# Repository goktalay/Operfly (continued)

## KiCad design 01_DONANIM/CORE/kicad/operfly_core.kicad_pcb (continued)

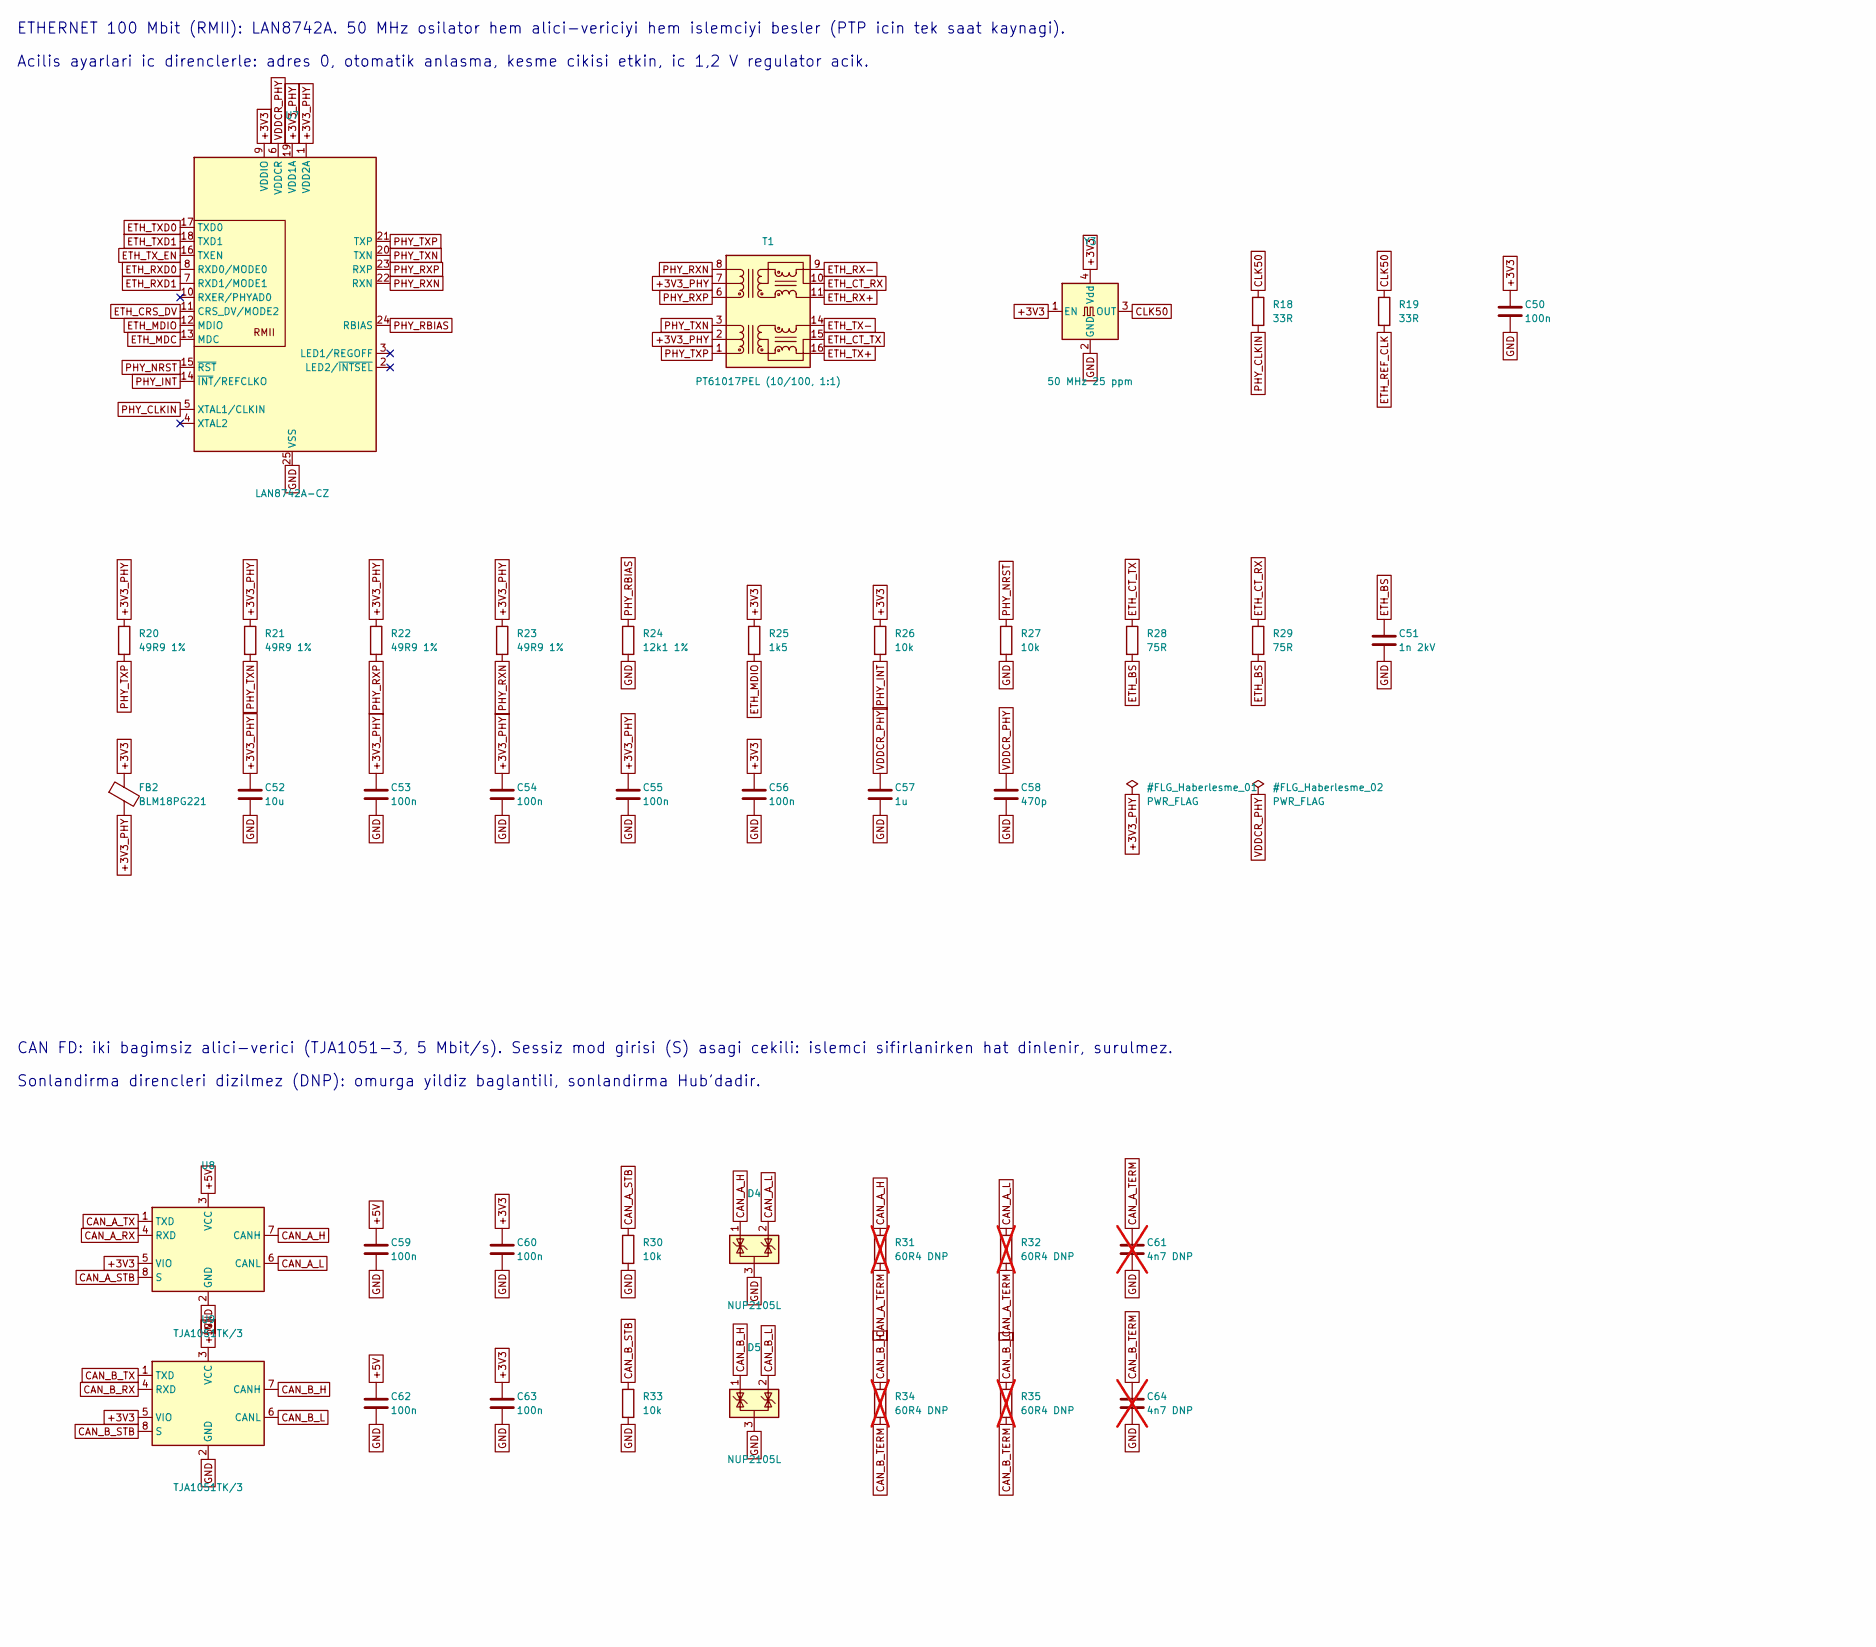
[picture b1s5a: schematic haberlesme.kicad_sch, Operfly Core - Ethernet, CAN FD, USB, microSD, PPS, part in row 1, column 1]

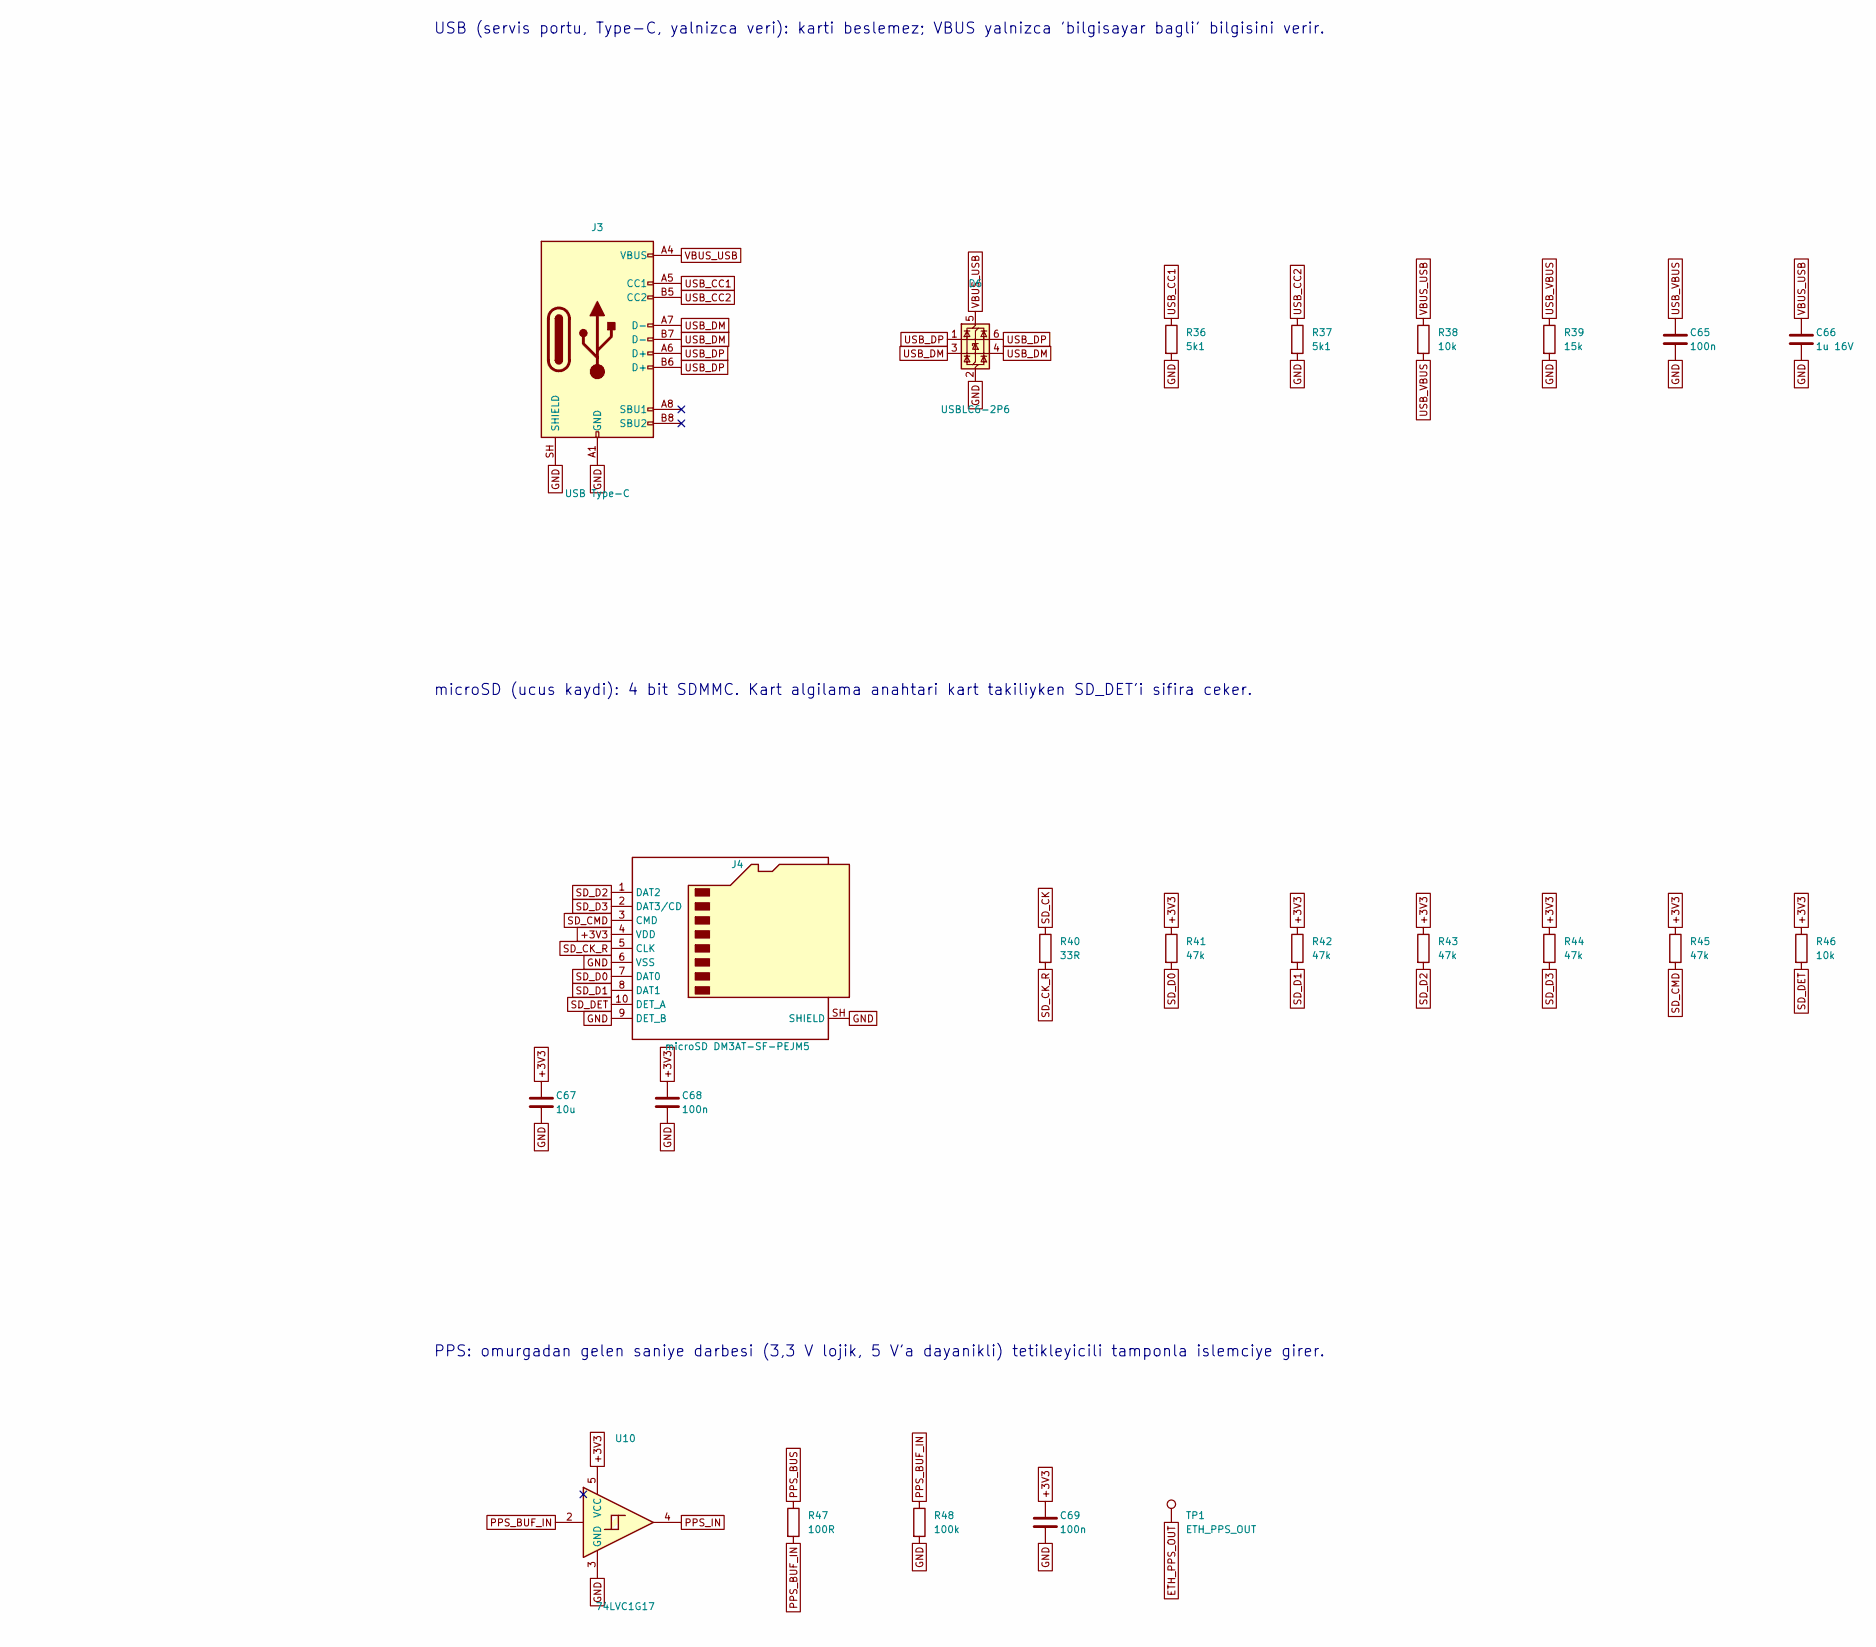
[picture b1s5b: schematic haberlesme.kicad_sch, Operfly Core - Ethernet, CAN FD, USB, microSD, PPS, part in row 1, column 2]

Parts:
C50, C53, C54, C55, C56, C59, C60, C62, C63, C65, C68, C69: 100n; C_0402_1005Metric
C51: 1n 2kV; C_1206_3216Metric
C52, C67: 10u; C_0805_2012Metric
C57: 1u; C_0402_1005Metric
C58: 470p; C_0402_1005Metric
C61, C64: 4n7 DNP; C_0402_1005Metric; not fitted
C66: 1u 16V; C_0603_1608Metric
D4, D5: NUP2105L; SOT-23
D6: USBLC6-2P6; SOT-666
FB2: BLM18PG221; L_0603_1608Metric
J3: USB Type-C; USB_C_Receptacle_GCT_USB4105-xx-A_16P_TopMnt_Horizontal
J4: microSD DM3AT-SF-PEJM5; microSD_HC_Hirose_DM3AT-SF-PEJM5
R18, R19, R40: 33R; R_0402_1005Metric
R20, R21, R22, R23: 49R9 1%; R_0402_1005Metric
R24: 12k1 1%; R_0402_1005Metric
R25: 1k5; R_0402_1005Metric
R26, R27, R30, R33, R38, R46: 10k; R_0402_1005Metric
R28, R29: 75R; R_0402_1005Metric
R31, R32, R34, R35: 60R4 DNP; R_0402_1005Metric; not fitted
R36, R37: 5k1; R_0402_1005Metric
R39: 15k; R_0402_1005Metric
R41, R42, R43, R44, R45: 47k; R_0402_1005Metric
R47: 100R; R_0402_1005Metric
R48: 100k; R_0402_1005Metric
T1: PT61017PEL (10/100, 1:1); Transformer_Ethernet_Bourns_PT61017PEL
TP1: ETH_PPS_OUT; TestPoint_Pad_D1.0mm
U7: LAN8742A-CZ; VQFN-24-1EP_4x4mm_P0.5mm_EP2.5x2.5mm_ThermalVias
U8, U9: TJA1051TK/3; HVSON-8-1EP_3x3mm_P0.65mm_EP1.6x2.4mm
U10: 74LVC1G17; SOT-353_SC-70-5
Y3: 50 MHz 25 ppm; Oscillator_SMD_Abracon_ASE-4Pin_3.2x2.5mm

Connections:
+3V3: C50.1, C56.1, C60.1, C63.1, C67.1, C68.1, C69.1, FB2.1, J4.4 (VDD), R25.1, R26.1, R41.1, R42.1, R43.1, R44.1, R45.1, R46.1, U7.9 (VDDIO), U8.5 (VIO), U9.5 (VIO), U10.5 (VCC), Y3.1 (EN), Y3.4 (Vdd); also elsewhere on the board
+3V3_PHY: C52.1, C53.1, C54.1, C55.1, FB2.2, R20.1, R21.1, R22.1, R23.1, T1.2 (C_TD), T1.7 (C_RD), U7.1 (VDD2A), U7.19 (VDD1A)
+5V: C59.1, C62.1, U8.3 (VCC), U9.3 (VCC); also elsewhere on the board
CAN_A_H: D4.1 (K), R31.1, U8.7 (CANH); also elsewhere on the board
CAN_A_L: D4.2 (K), R32.1, U8.6 (CANL); also elsewhere on the board
CAN_A_RX: U8.4 (RXD); also elsewhere on the board
CAN_A_STB: R30.1, U8.8 (S); also elsewhere on the board
CAN_A_TERM: C61.1, R31.2, R32.2
CAN_A_TX: U8.1 (TXD); also elsewhere on the board
CAN_B_H: D5.1 (K), R34.1, U9.7 (CANH); also elsewhere on the board
CAN_B_L: D5.2 (K), R35.1, U9.6 (CANL); also elsewhere on the board
CAN_B_RX: U9.4 (RXD); also elsewhere on the board
CAN_B_STB: R33.1, U9.8 (S); also elsewhere on the board
CAN_B_TERM: C64.1, R34.2, R35.2
CAN_B_TX: U9.1 (TXD); also elsewhere on the board
CLK50: R18.1, R19.1, Y3.3 (OUT)
ETH_BS: C51.1, R28.2, R29.2
ETH_CRS_DV: U7.11 (CRS_DV/MODE2); also elsewhere on the board
ETH_CT_RX: R29.1, T1.10 (C_RX)
ETH_CT_TX: R28.1, T1.15 (C_TX)
ETH_MDC: U7.13 (MDC); also elsewhere on the board
ETH_MDIO: R25.2, U7.12 (MDIO); also elsewhere on the board
ETH_PPS_OUT: TP1.1; also elsewhere on the board
ETH_REF_CLK: R19.2; also elsewhere on the board
ETH_RX+: T1.11 (RX+); also elsewhere on the board
ETH_RX-: T1.9 (RX-); also elsewhere on the board
ETH_RXD0: U7.8 (RXD0/MODE0); also elsewhere on the board
ETH_RXD1: U7.7 (RXD1/MODE1); also elsewhere on the board
ETH_TX+: T1.16 (TX+); also elsewhere on the board
ETH_TX-: T1.14 (TX-); also elsewhere on the board
ETH_TXD0: U7.17 (TXD0); also elsewhere on the board
ETH_TXD1: U7.18 (TXD1); also elsewhere on the board
ETH_TX_EN: U7.16 (TXEN); also elsewhere on the board
GND: C50.2, C51.2, C52.2, C53.2, C54.2, C55.2, C56.2, C57.2, C58.2, C59.2, C60.2, C61.2, C62.2, C63.2, C64.2, C65.2, C66.2, C67.2, C68.2, C69.2, D4.3 (A), D5.3 (A), D6.2 (GND), J3.A1 (GND), J3.A12 (GND), J3.B1 (GND), J3.B12 (GND), J3.SH (SHIELD), J4.6 (VSS), J4.9 (DET_B), J4.SH (SHIELD), R24.2, R27.2, R30.2, R33.2, R36.2, R37.2, R39.2, R48.2, U7.25 (VSS), U8.2 (GND), U8.9 (GND), U9.2 (GND), U9.9 (GND), U10.3 (GND), Y3.2 (GND); also elsewhere on the board
PHY_CLKIN: R18.2, U7.5 (XTAL1/CLKIN)
PHY_INT: R26.2, U7.14 (~INT/REFCLKO); also elsewhere on the board
PHY_NRST: R27.1, U7.15 (~RST); also elsewhere on the board
PHY_RBIAS: R24.1, U7.24 (RBIAS)
PHY_RXN: R23.2, T1.8 (RD-), U7.22 (RXN)
PHY_RXP: R22.2, T1.6 (RD+), U7.23 (RXP)
PHY_TXN: R21.2, T1.3 (TD-), U7.20 (TXN)
PHY_TXP: R20.2, T1.1 (TD+), U7.21 (TXP)
PPS_BUF_IN: R47.2, R48.1, U10.2
PPS_BUS: R47.1; also elsewhere on the board
PPS_IN: U10.4; also elsewhere on the board
SD_CK: R40.1; also elsewhere on the board
SD_CK_R: J4.5 (CLK), R40.2
SD_CMD: J4.3 (CMD), R45.2; also elsewhere on the board
SD_D0: J4.7 (DAT0), R41.2; also elsewhere on the board
SD_D1: J4.8 (DAT1), R42.2; also elsewhere on the board
SD_D2: J4.1 (DAT2), R43.2; also elsewhere on the board
SD_D3: J4.2 (DAT3/CD), R44.2; also elsewhere on the board
SD_DET: J4.10 (DET_A), R46.2; also elsewhere on the board
USB_CC1: J3.A5 (CC1), R36.1
USB_CC2: J3.B5 (CC2), R37.1
USB_DM: D6.3 (I/O2), D6.4 (I/O2), J3.A7 (D-), J3.B7 (D-); also elsewhere on the board
USB_DP: D6.1 (I/O1), D6.6 (I/O1), J3.A6 (D+), J3.B6 (D+); also elsewhere on the board
USB_VBUS: C65.1, R38.2, R39.1; also elsewhere on the board
VBUS_USB: C66.1, D6.5 (VBUS), J3.A4 (VBUS), J3.A9 (VBUS), J3.B4 (VBUS), J3.B9 (VBUS), R38.1
VDDCR_PHY: C57.1, C58.1, U7.6 (VDDCR)

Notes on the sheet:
Acilis ayarlari ic direnclerle: adres 0, otomatik anlasma, kesme cikisi etkin, ic 1,2 V regulator acik.
PPS: omurgadan gelen saniye darbesi (3,3 V lojik, 5 V'a dayanikli) tetikleyicili tamponla islemciye girer.
USB (servis portu, Type-C, yalnizca veri): karti beslemez; VBUS yalnizca 'bilgisayar bagli' bilgisini verir.
microSD (ucus kaydi): 4 bit SDMMC. Kart algilama anahtari kart takiliyken SD_DET'i sifira ceker.
ETHERNET 100 Mbit (RMII): LAN8742A. 50 MHz osilator hem alici-vericiyi hem islemciyi besler (PTP icin tek saat kaynagi).
CAN FD: iki bagimsiz alici-verici (TJA1051-3, 5 Mbit/s). Sessiz mod girisi (S) asagi cekili: islemci sifirlanirken hat dinlenir, surulmez.
Sonlandirma direncleri dizilmez (DNP): omurga yildiz baglantili, sonlandirma Hub'dadir.

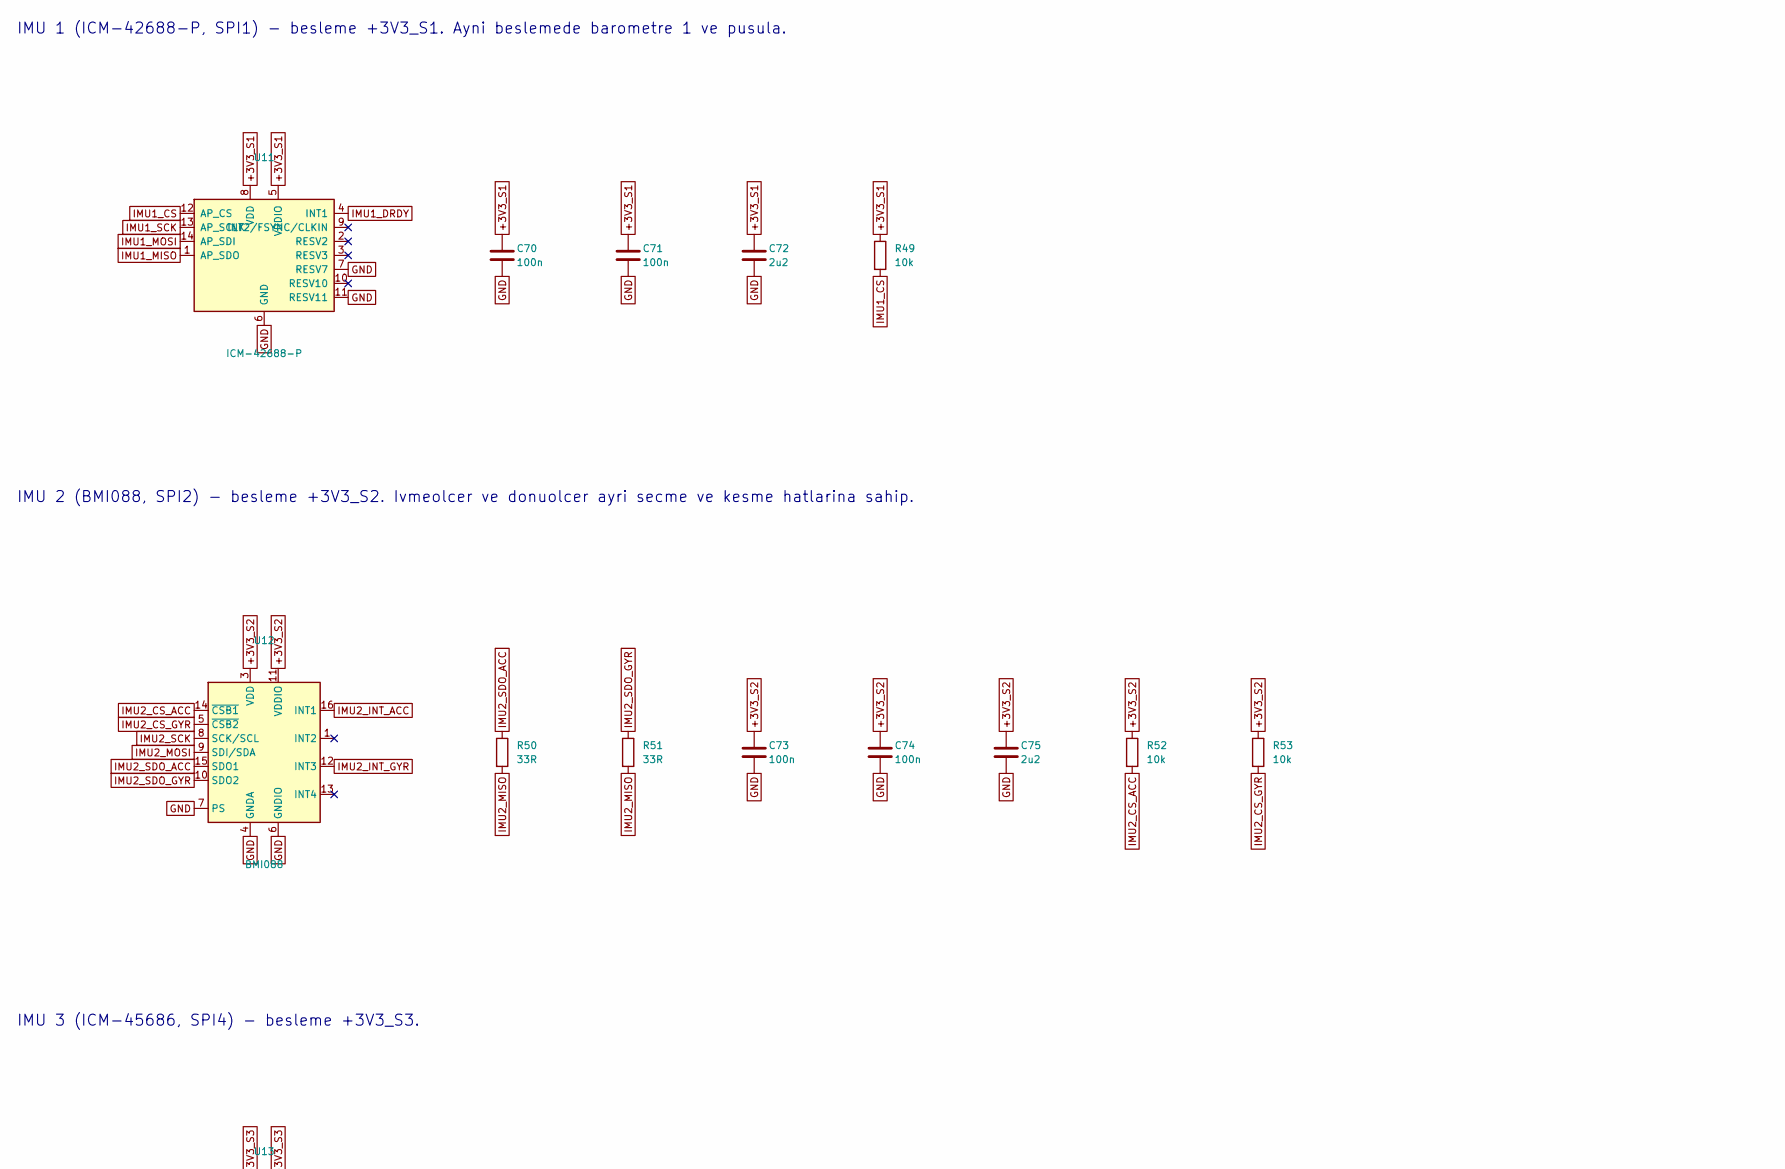
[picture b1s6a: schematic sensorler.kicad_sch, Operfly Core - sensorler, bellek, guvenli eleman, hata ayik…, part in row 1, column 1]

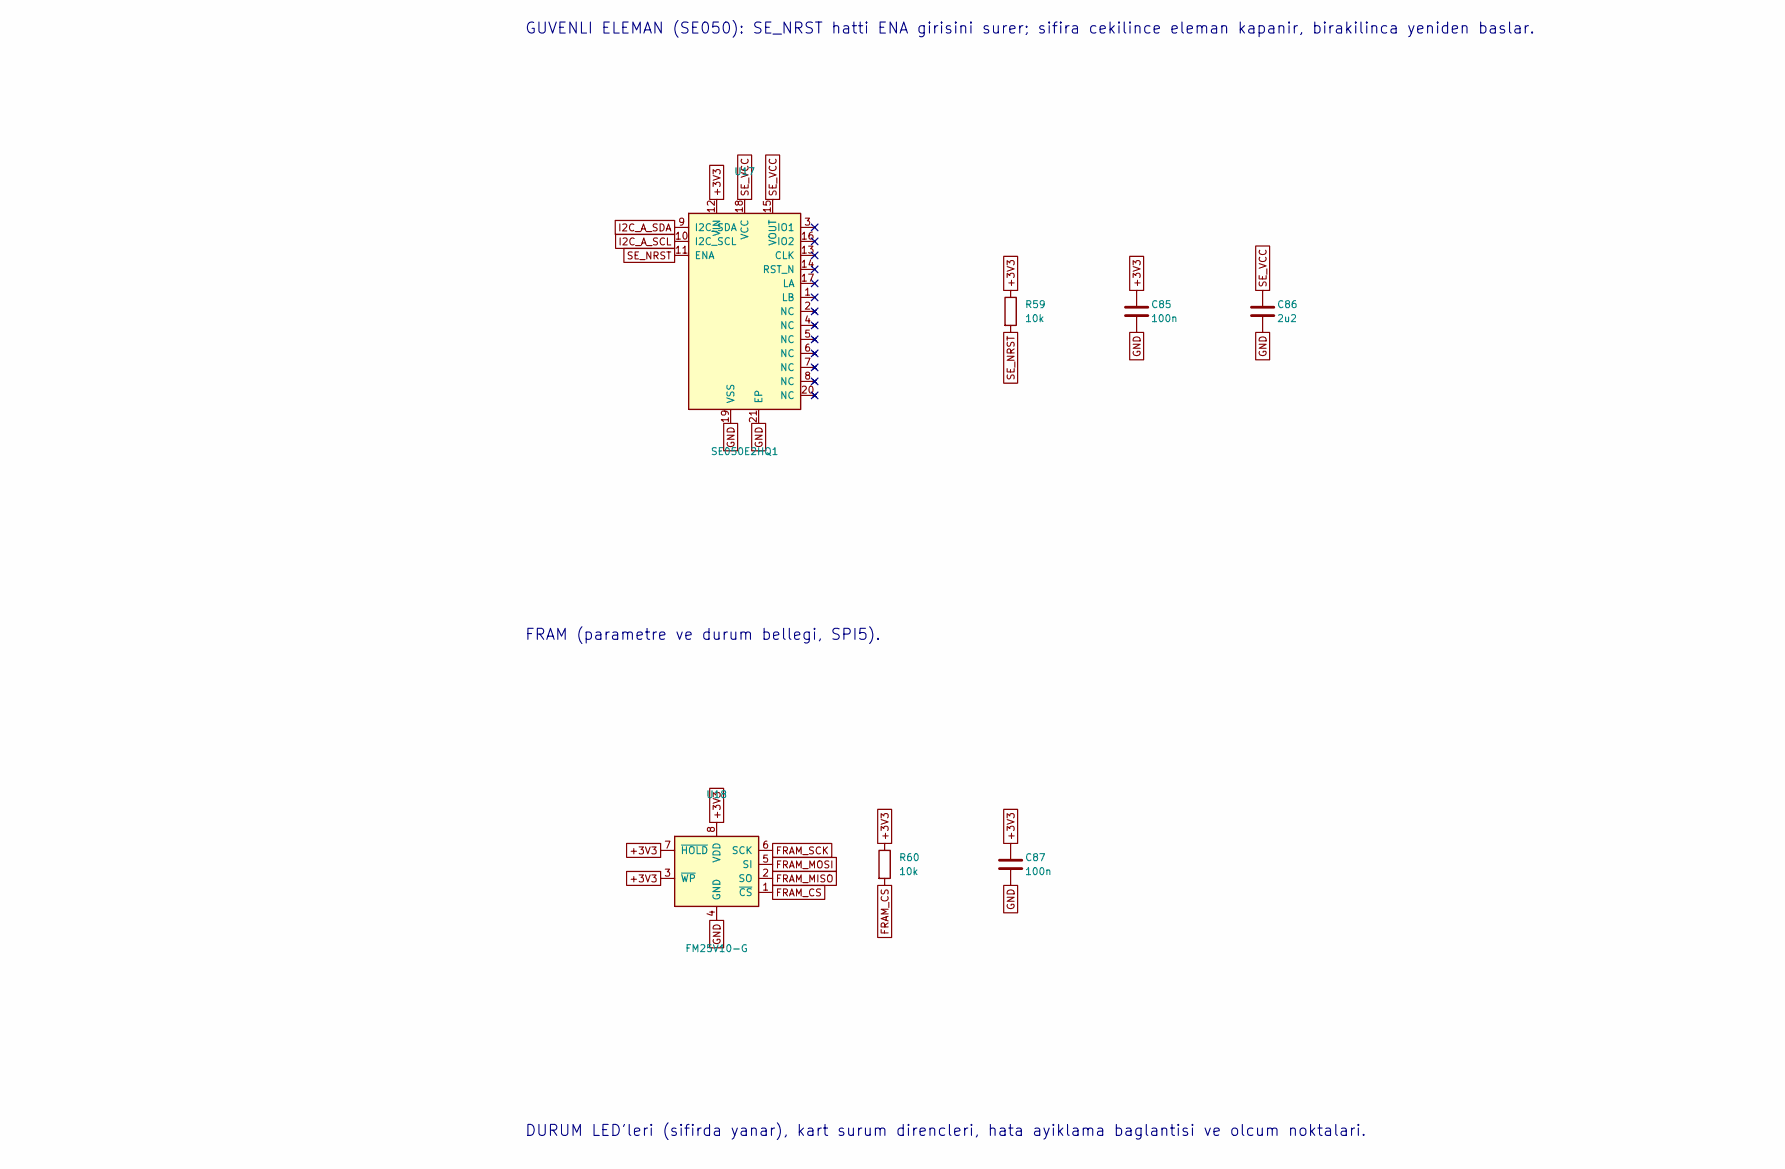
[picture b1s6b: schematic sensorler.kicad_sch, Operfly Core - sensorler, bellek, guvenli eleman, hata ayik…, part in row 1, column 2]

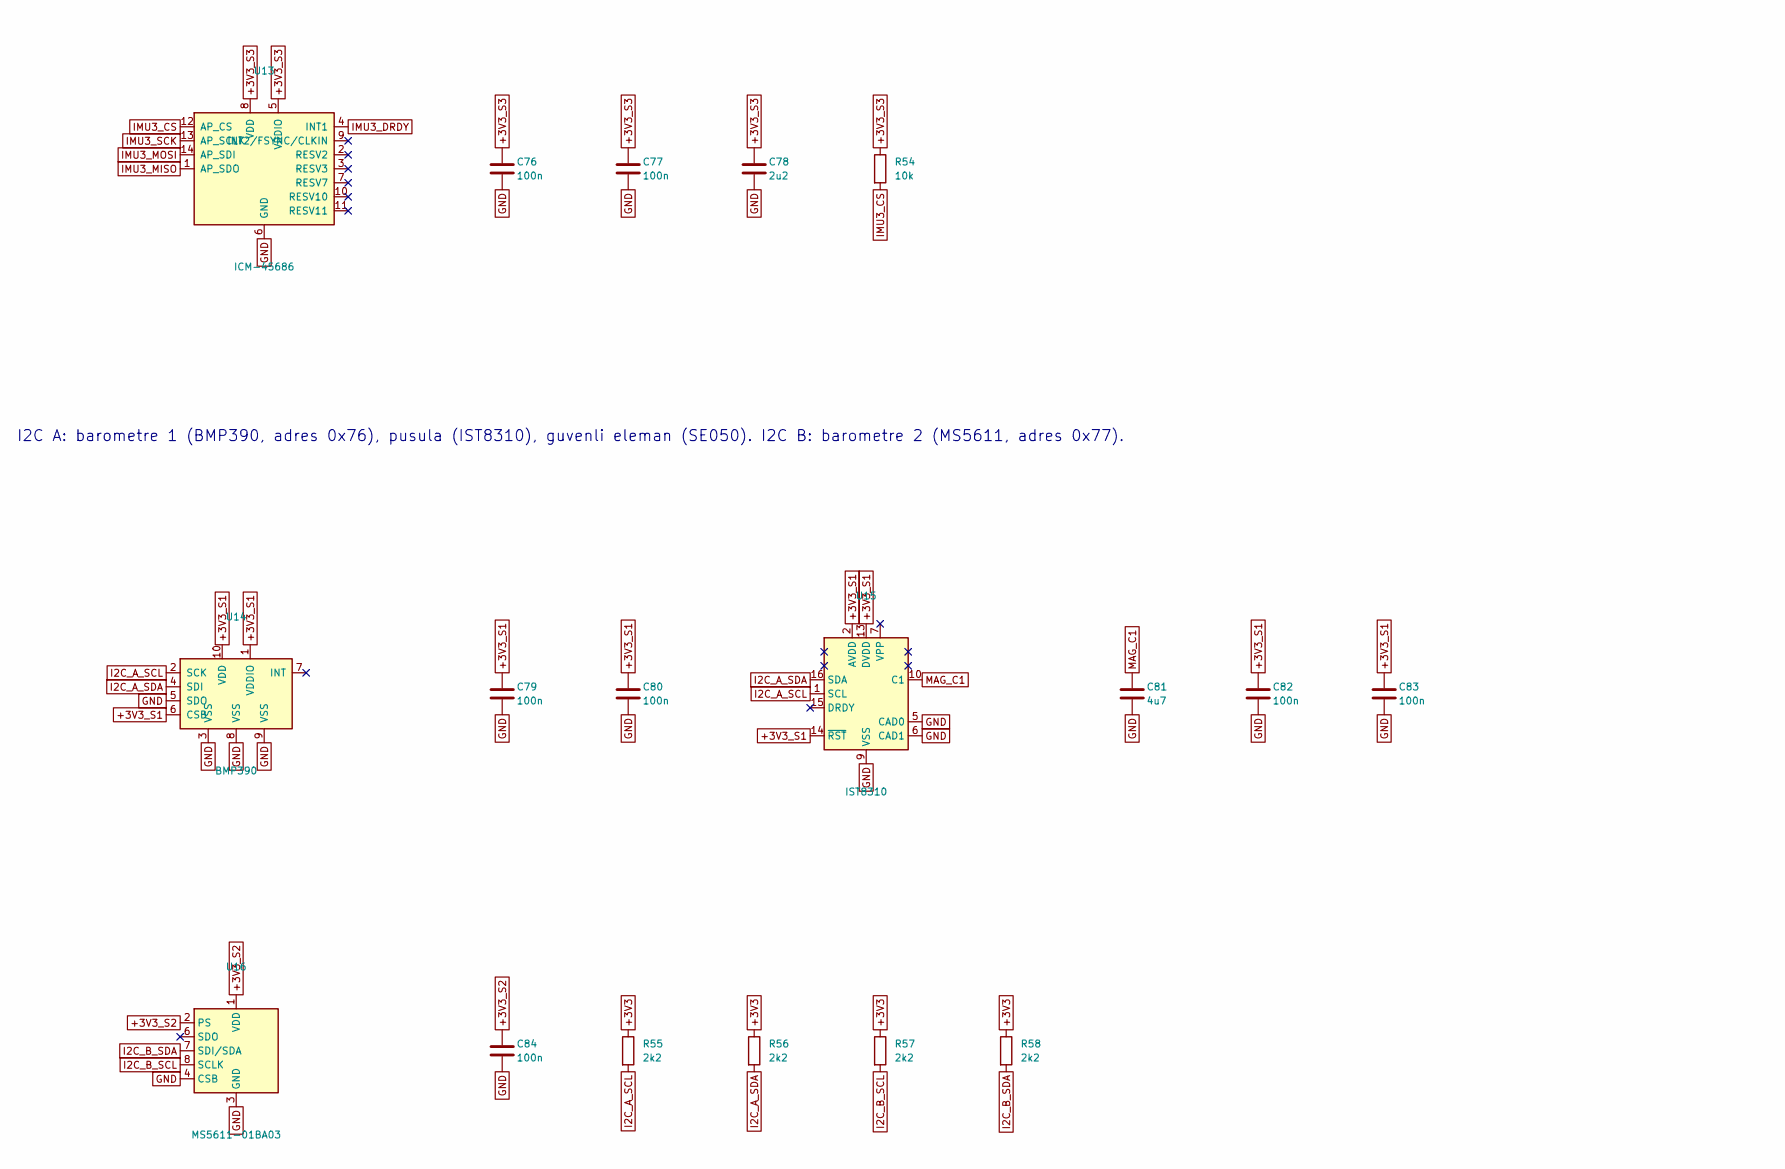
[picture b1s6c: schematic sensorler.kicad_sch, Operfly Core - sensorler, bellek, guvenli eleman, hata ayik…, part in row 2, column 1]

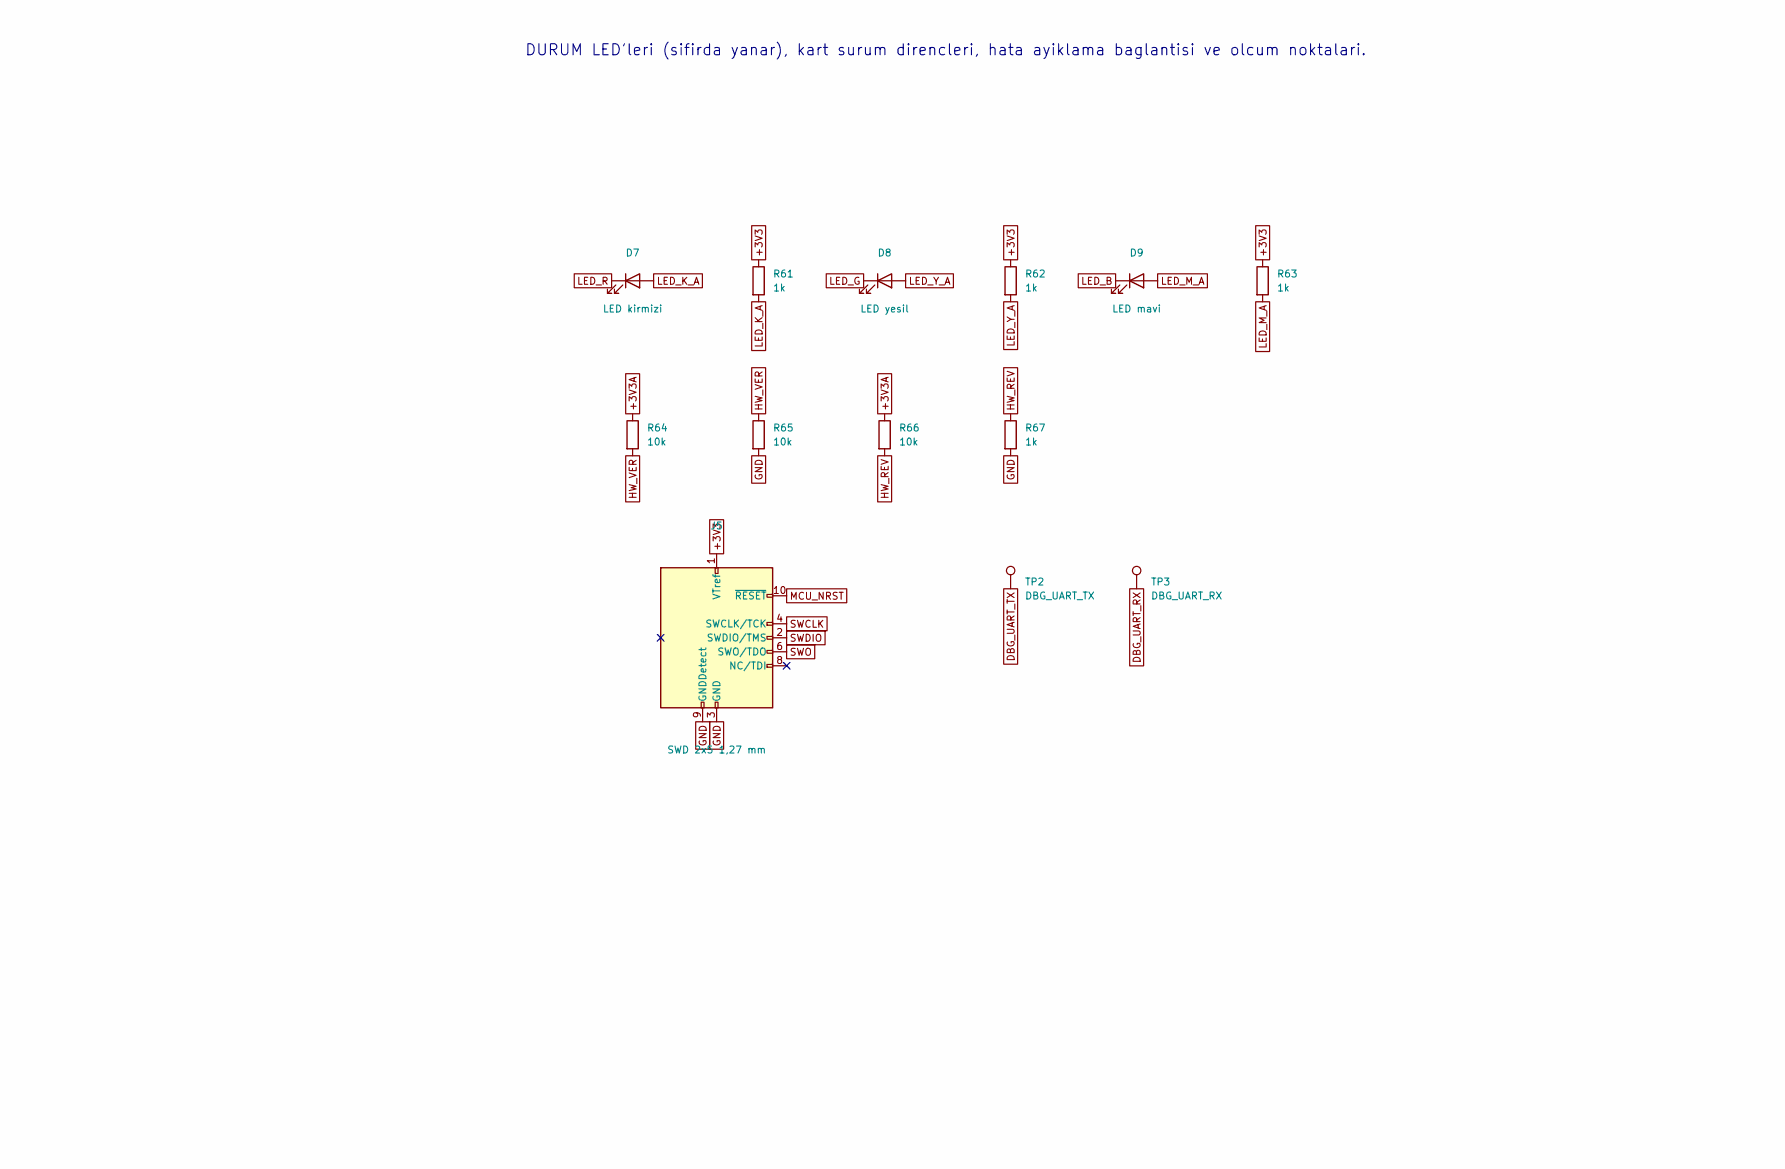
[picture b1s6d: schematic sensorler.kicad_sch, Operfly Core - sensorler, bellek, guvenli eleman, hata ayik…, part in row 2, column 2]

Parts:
C70, C71, C73, C74, C76, C77, C79, C80, C82, C83, C84, C85, C87: 100n; C_0402_1005Metric
C72, C75, C78, C86: 2u2; C_0603_1608Metric
C81: 4u7; C_0603_1608Metric
D7: LED kirmizi; LED_0603_1608Metric
D8: LED yesil; LED_0603_1608Metric
D9: LED mavi; LED_0603_1608Metric
J5: SWD 2x5 1,27 mm; PinHeader_2x05_P1.27mm_Vertical_SMD
R49, R52, R53, R54, R59, R60, R64, R65, R66: 10k; R_0402_1005Metric
R50, R51: 33R; R_0402_1005Metric
R55, R56, R57, R58: 2k2; R_0402_1005Metric
R61, R62, R63, R67: 1k; R_0402_1005Metric
TP2: DBG_UART_TX; TestPoint_Pad_D1.0mm
TP3: DBG_UART_RX; TestPoint_Pad_D1.0mm
U11: ICM-42688-P; Bosch_LGA-14_3x2.5mm_P0.5mm
U12: BMI088; Bosch_LGA-16_4.5x3mm_P0.5mm_LayoutBorder7x1y_ClockwisePinNu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
U13: ICM-45686; Bosch_LGA-14_3x2.5mm_P0.5mm
U14: BMP390; ST_HLGA-10_2x2mm_P0.5mm_LayoutBorder3x2y
U15: IST8310; LGA-16_3x3mm_P0.5mm
U16: MS5611-01BA03; LGA-8_3x5mm_P1.25mm
U17: SE050E2HQ1; QFN-20-1EP_3x3mm_P0.4mm_EP1.65x1.65mm
U18: FM25V10-G; SOIC-8_3.9x4.9mm_P1.27mm

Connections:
+3V3: C85.1, C87.1, J5.1 (VTref), R55.1, R56.1, R57.1, R58.1, R59.1, R60.1, R61.1, R62.1, R63.1, U17.12 (VIN), U18.3 (~WP), U18.7 (~HOLD), U18.8 (VDD); also elsewhere on the board
+3V3A: R64.1, R66.1; also elsewhere on the board
+3V3_S1: C70.1, C71.1, C72.1, C79.1, C80.1, C82.1, C83.1, R49.1, U11.5 (VDDIO), U11.8 (VDD), U14.1 (VDDIO), U14.6 (CSB), U14.10 (VDD), U15.2 (AVDD), U15.13 (DVDD), U15.14 (~RST); also elsewhere on the board
+3V3_S2: C73.1, C74.1, C75.1, C84.1, R52.1, R53.1, U12.3 (VDD), U12.11 (VDDIO), U16.1 (VDD), U16.2 (PS); also elsewhere on the board
+3V3_S3: C76.1, C77.1, C78.1, R54.1, U13.5 (VDDIO), U13.8 (VDD); also elsewhere on the board
DBG_UART_RX: TP3.1; also elsewhere on the board
DBG_UART_TX: TP2.1; also elsewhere on the board
FRAM_CS: R60.2, U18.1 (~CS); also elsewhere on the board
FRAM_MISO: U18.2 (SO); also elsewhere on the board
FRAM_MOSI: U18.5 (SI); also elsewhere on the board
FRAM_SCK: U18.6 (SCK); also elsewhere on the board
GND: C70.2, C71.2, C72.2, C73.2, C74.2, C75.2, C76.2, C77.2, C78.2, C79.2, C80.2, C81.2, C82.2, C83.2, C84.2, C85.2, C86.2, C87.2, J5.3 (GND), J5.5 (GND), J5.9 (GNDDetect), R65.2, R67.2, U11.6 (GND), U11.7 (RESV7), U11.11 (RESV11), U12.2 (GNDA), U12.4 (GNDA), U12.6 (GNDIO), U12.7 (PS), U13.6 (GND), U14.3 (VSS), U14.5 (SDO), U14.8 (VSS), U14.9 (VSS), U15.5 (CAD0), U15.6 (CAD1), U15.9 (VSS), U15.11 (VSS), U16.3 (GND), U16.4 (CSB), U16.5 (CSB), U17.19 (VSS), U17.21 (EP), U18.4 (GND); also elsewhere on the board
HW_REV: R66.2, R67.1; also elsewhere on the board
HW_VER: R64.2, R65.1; also elsewhere on the board
I2C_A_SCL: R55.2, U14.2 (SCK), U15.1 (SCL), U17.10 (I2C_SCL); also elsewhere on the board
I2C_A_SDA: R56.2, U14.4 (SDI), U15.16 (SDA), U17.9 (I2C_SDA); also elsewhere on the board
I2C_B_SCL: R57.2, U16.8 (SCLK); also elsewhere on the board
I2C_B_SDA: R58.2, U16.7 (SDI/SDA); also elsewhere on the board
IMU1_CS: R49.2, U11.12 (AP_CS); also elsewhere on the board
IMU1_DRDY: U11.4 (INT1); also elsewhere on the board
IMU1_MISO: U11.1 (AP_SDO); also elsewhere on the board
IMU1_MOSI: U11.14 (AP_SDI); also elsewhere on the board
IMU1_SCK: U11.13 (AP_SCLK); also elsewhere on the board
IMU2_CS_ACC: R52.2, U12.14 (~CSB1); also elsewhere on the board
IMU2_CS_GYR: R53.2, U12.5 (~CSB2); also elsewhere on the board
IMU2_INT_ACC: U12.16 (INT1); also elsewhere on the board
IMU2_INT_GYR: U12.12 (INT3); also elsewhere on the board
IMU2_MISO: R50.2, R51.2; also elsewhere on the board
IMU2_MOSI: U12.9 (SDI/SDA); also elsewhere on the board
IMU2_SCK: U12.8 (SCK/SCL); also elsewhere on the board
IMU2_SDO_ACC: R50.1, U12.15 (SDO1)
IMU2_SDO_GYR: R51.1, U12.10 (SDO2)
IMU3_CS: R54.2, U13.12 (AP_CS); also elsewhere on the board
IMU3_DRDY: U13.4 (INT1); also elsewhere on the board
IMU3_MISO: U13.1 (AP_SDO); also elsewhere on the board
IMU3_MOSI: U13.14 (AP_SDI); also elsewhere on the board
IMU3_SCK: U13.13 (AP_SCLK); also elsewhere on the board
LED_B: D9.1 (K); also elsewhere on the board
LED_G: D8.1 (K); also elsewhere on the board
LED_K_A: D7.2 (A), R61.2
LED_M_A: D9.2 (A), R63.2
LED_R: D7.1 (K); also elsewhere on the board
LED_Y_A: D8.2 (A), R62.2
MAG_C1: C81.1, U15.10 (C1)
MCU_NRST: J5.10 (~RESET); also elsewhere on the board
SE_NRST: R59.2, U17.11 (ENA); also elsewhere on the board
SE_VCC: C86.1, U17.15 (VOUT), U17.18 (VCC)
SWCLK: J5.4 (SWCLK/TCK); also elsewhere on the board
SWDIO: J5.2 (SWDIO/TMS); also elsewhere on the board
SWO: J5.6 (SWO/TDO); also elsewhere on the board

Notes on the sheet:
I2C A: barometre 1 (BMP390, adres 0x76), pusula (IST8310), guvenli eleman (SE050). I2C B: barometre 2 (MS5611, adres 0x77).
FRAM (parametre ve durum bellegi, SPI5).
IMU 2 (BMI088, SPI2) - besleme +3V3_S2. Ivmeolcer ve donuolcer ayri secme ve kesme hatlarina sahip.
DURUM LED'leri (sifirda yanar), kart surum direncleri, hata ayiklama baglantisi ve olcum noktalari.
IMU 3 (ICM-45686, SPI4) - besleme +3V3_S3.
IMU 1 (ICM-42688-P, SPI1) - besleme +3V3_S1. Ayni beslemede barometre 1 ve pusula.
GUVENLI ELEMAN (SE050): SE_NRST hatti ENA girisini surer; sifira cekilince eleman kapanir, birakilinca yeniden baslar.

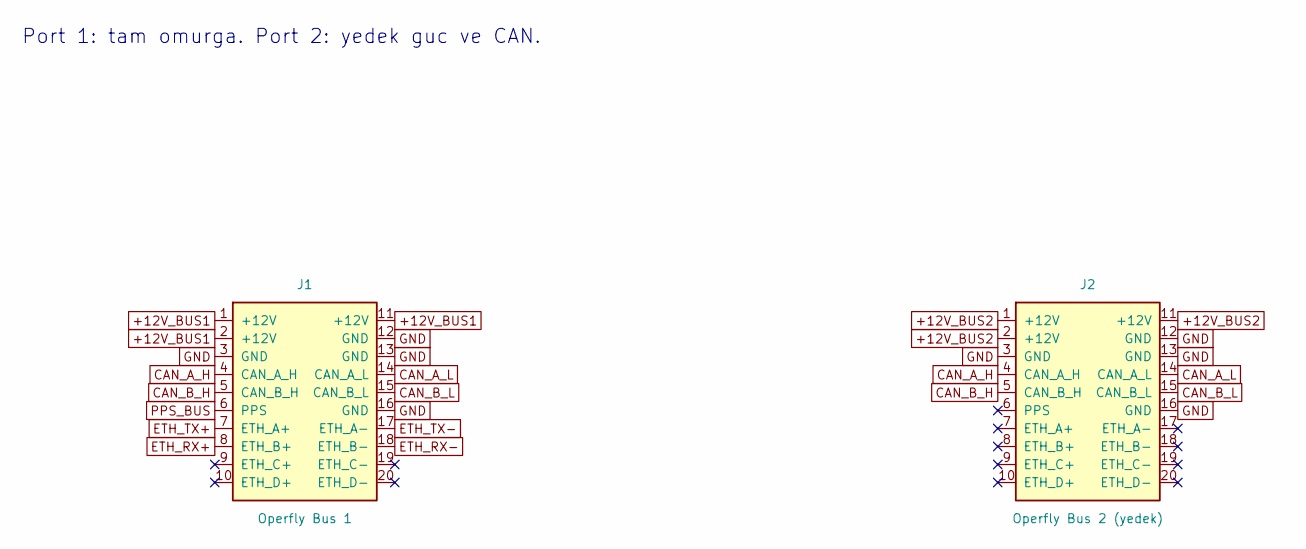
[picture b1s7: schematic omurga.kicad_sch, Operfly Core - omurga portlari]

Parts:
J1: Operfly Bus 1; Harwin_Gecko_G125-MS12005M2P_2x10_P1.25mm_Vertical
J2: Operfly Bus 2 (yedek); Harwin_Gecko_G125-MS12005M2P_2x10_P1.25mm_Vertical

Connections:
+12V_BUS1: J1.1 (+12V), J1.2 (+12V), J1.11 (+12V); also elsewhere on the board
+12V_BUS2: J2.1 (+12V), J2.2 (+12V), J2.11 (+12V); also elsewhere on the board
CAN_A_H: J1.4 (CAN_A_H), J2.4 (CAN_A_H); also elsewhere on the board
CAN_A_L: J1.14 (CAN_A_L), J2.14 (CAN_A_L); also elsewhere on the board
CAN_B_H: J1.5 (CAN_B_H), J2.5 (CAN_B_H); also elsewhere on the board
CAN_B_L: J1.15 (CAN_B_L), J2.15 (CAN_B_L); also elsewhere on the board
ETH_RX+: J1.8 (ETH_B+); also elsewhere on the board
ETH_RX-: J1.18 (ETH_B-); also elsewhere on the board
ETH_TX+: J1.7 (ETH_A+); also elsewhere on the board
ETH_TX-: J1.17 (ETH_A-); also elsewhere on the board
GND: J1.3 (GND), J1.12 (GND), J1.13 (GND), J1.16 (GND), J2.3 (GND), J2.12 (GND), J2.13 (GND), J2.16 (GND); also elsewhere on the board
PPS_BUS: J1.6 (PPS); also elsewhere on the board

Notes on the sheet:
Port 1: tam omurga. Port 2: yedek guc ve CAN.
